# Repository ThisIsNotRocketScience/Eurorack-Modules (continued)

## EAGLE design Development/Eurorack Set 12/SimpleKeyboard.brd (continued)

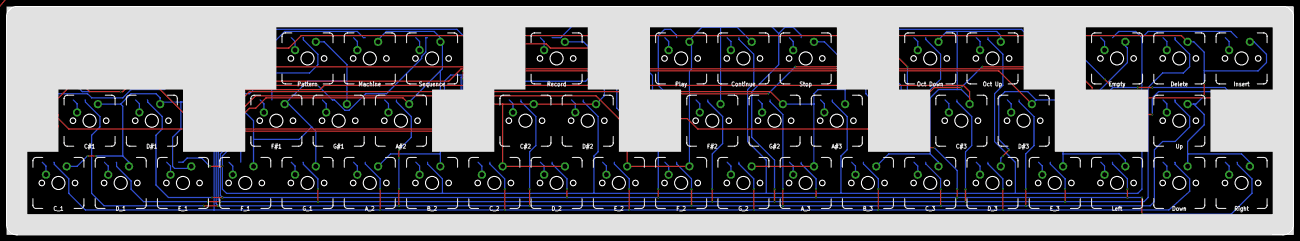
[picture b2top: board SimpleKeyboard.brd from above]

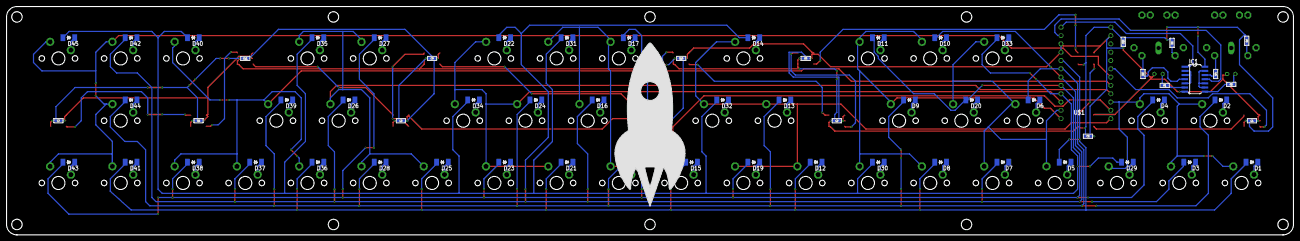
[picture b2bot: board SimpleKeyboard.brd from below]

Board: 2 copper layers, 393.7 x 69.8 mm, 152 parts (66 on the bottom side), 87 nets.

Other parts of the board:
U$45: ROCKET-5CM

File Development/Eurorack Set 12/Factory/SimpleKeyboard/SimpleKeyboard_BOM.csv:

Comment,Designator,Footprint,LCSC Part #
CGRM4001-G,"D1, D10, D11, D12, D13, D14, D15, D16, D17, D18, D19, D2, D20, D21, D22, D23, D24, D25, D26, D27, D28, D3, D4, D5, D6, D7, D8, D9, D29, D30, D31, D32, D33, D34, D35, D36, D37, D38, D39, D40, D41, D42, D43, D44, D45",SOD-123_MINI-SMA,
ARDUINO_PRO_MICRO,"U$1",ARDUINO_PRO_MICRO,
WS2812B,"LED1, LED2, LED3, LED4, LED5, LED6, LED7, LED8, LED9, LED10, LED11, LED12",WS2812B,
100n,"C1, C2, C3, C4, C5, C6, C7, C8, C9, C10, C11, C12",C0603,
MIDIJACK,"U$4, U$11",CP-2350,
74AC04D,"IC1",SO14,
330,"R1, R2",R0603,
220,"R3, R4, R5, R6",R0603,
,"D46, D47",3MMLED,
BUBBLESDSA_1U,"U$15, U$16, U$17, U$18, U$19, U$20",BUBBLES,
BUBBLESDSA_1U_HALF,"U$21, U$22, U$33",BUBBLES_HALF,
BUBBLESINV,"U$28, U$29, U$30, U$31, U$32",BUBBLES_INV,
BUBBLESONE,"U$34, U$35, U$36, U$37, U$38, U$39, U$40, U$41, U$42, U$43, U$44",BUBBLES_ONE,
C_1,"SW46",MX1A-XXNW,
C#1,"SW47",MX1A-XXNW,
D_1,"SW48",MX1A-XXNW,
D#1,"SW49",MX1A-XXNW,
E_1,"SW50",MX1A-XXNW,
F_1,"SW51",MX1A-XXNW,
F#1,"SW52",MX1A-XXNW,
G_1,"SW53",MX1A-XXNW,
G#1,"SW54",MX1A-XXNW,
A_2,"SW55",MX1A-XXNW,
A#2,"SW56",MX1A-XXNW,
B_2,"SW57",MX1A-XXNW,
C_2,"SW58",MX1A-XXNW,
C#2,"SW59",MX1A-XXNW,
D_2,"SW60",MX1A-XXNW,
D#2,"SW61",MX1A-XXNW,
E_2,"SW62",MX1A-XXNW,
F_2,"SW63",MX1A-XXNW,
F#2,"SW64",MX1A-XXNW,
G_2,"SW65",MX1A-XXNW,
G#2,"SW66",MX1A-XXNW,
A_3,"SW67",MX1A-XXNW,
A#3,"SW68",MX1A-XXNW,
B_3,"SW69",MX1A-XXNW,
C_3,"SW70",MX1A-XXNW,
C#3,"SW71",MX1A-XXNW,
D_3,"SW72",MX1A-XXNW,
D#3,"SW73",MX1A-XXNW,
E_3,"SW74",MX1A-XXNW,
Right,"SW75",MX1A-XXNW,
Up,"SW76",MX1A-XXNW,
Down,"SW77",MX1A-XXNW,
Stop,"SW78",MX1A-XXNW,
Oct Down,"SW79",MX1A-XXNW,
Left,"SW80",MX1A-XXNW,
Play,"SW81",MX1A-XXNW,
Continue,"SW82",MX1A-XXNW,
Record,"SW83",MX1A-XXNW,
Empty,"SW84",MX1A-XXNW,
Oct Up,"SW85",MX1A-XXNW,
Delete,"SW86",MX1A-XXNW,
Insert,"SW87",MX1A-XXNW,
Sequence,"SW88",MX1A-XXNW,
Pattern,"SW89",MX1A-XXNW,
Machine,"SW90",MX1A-XXNW,

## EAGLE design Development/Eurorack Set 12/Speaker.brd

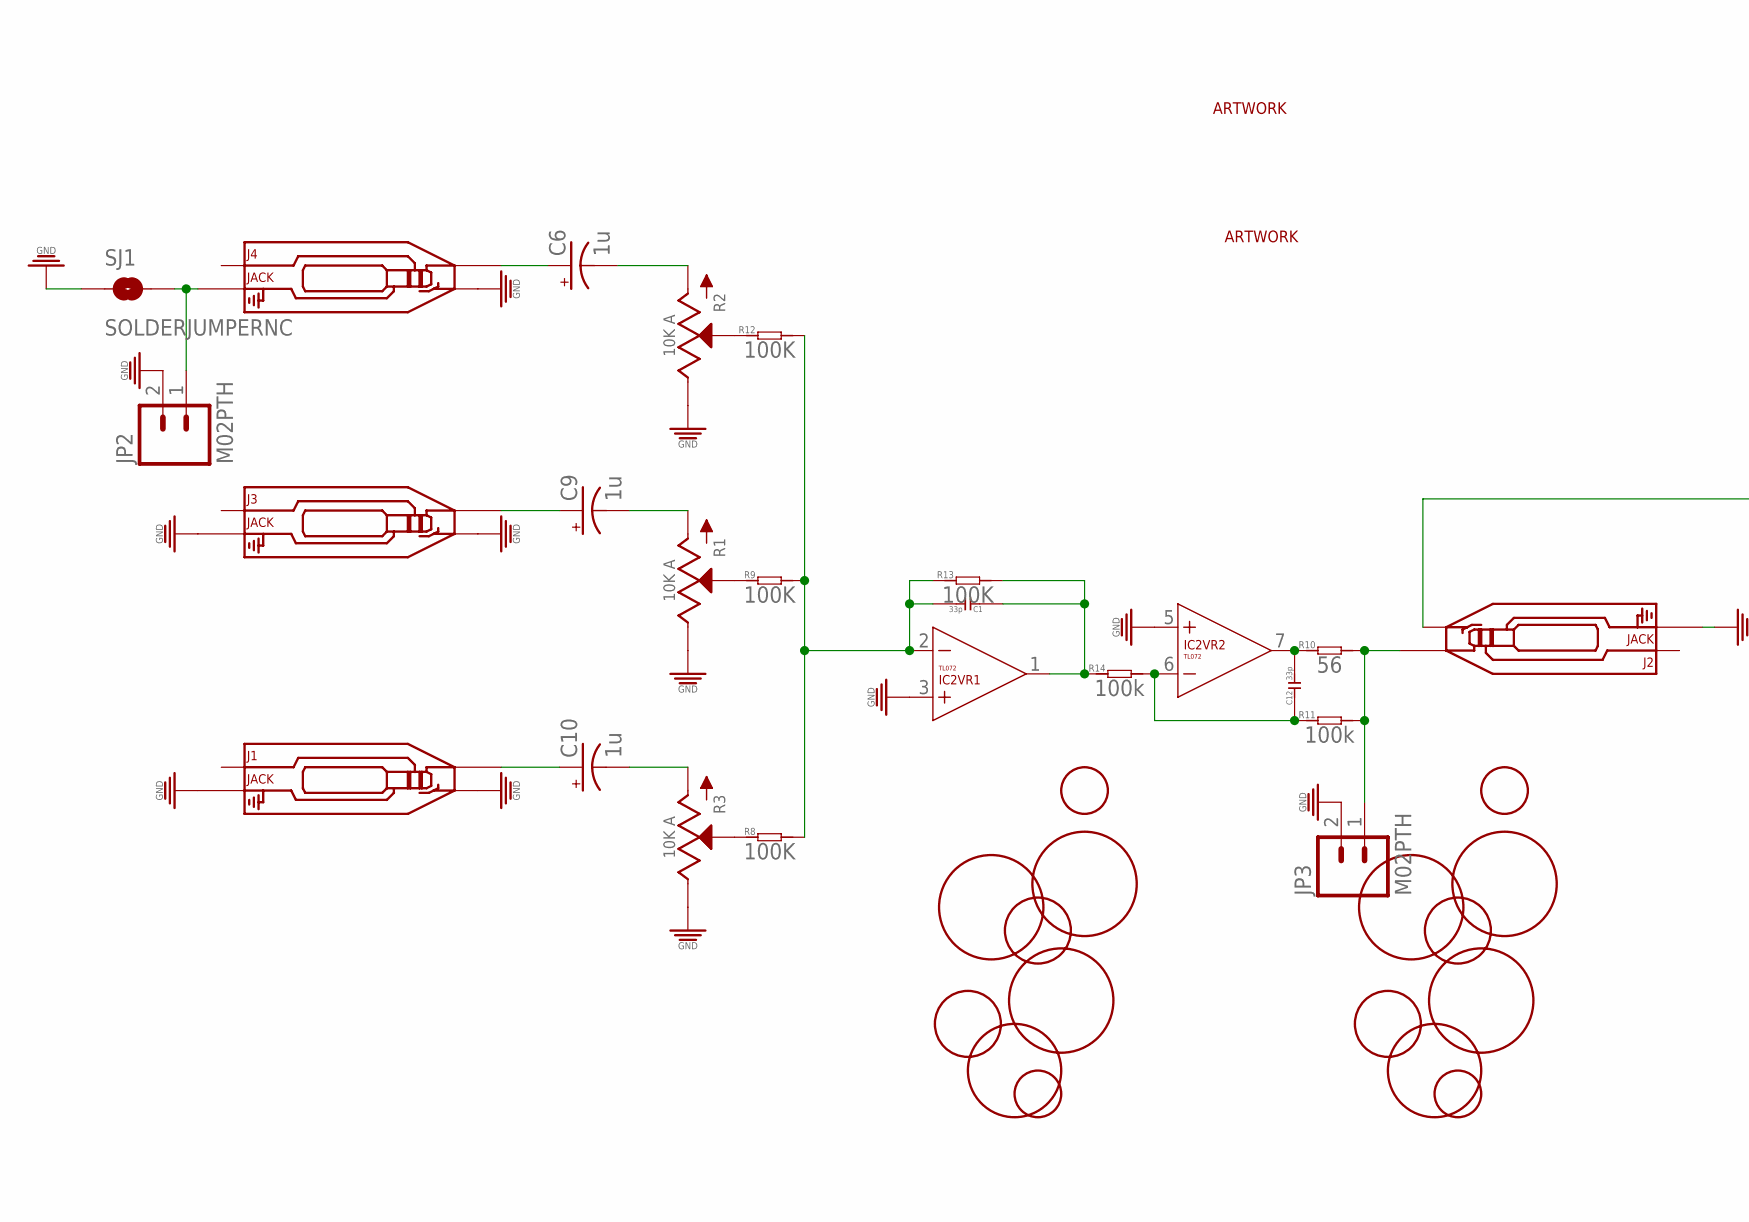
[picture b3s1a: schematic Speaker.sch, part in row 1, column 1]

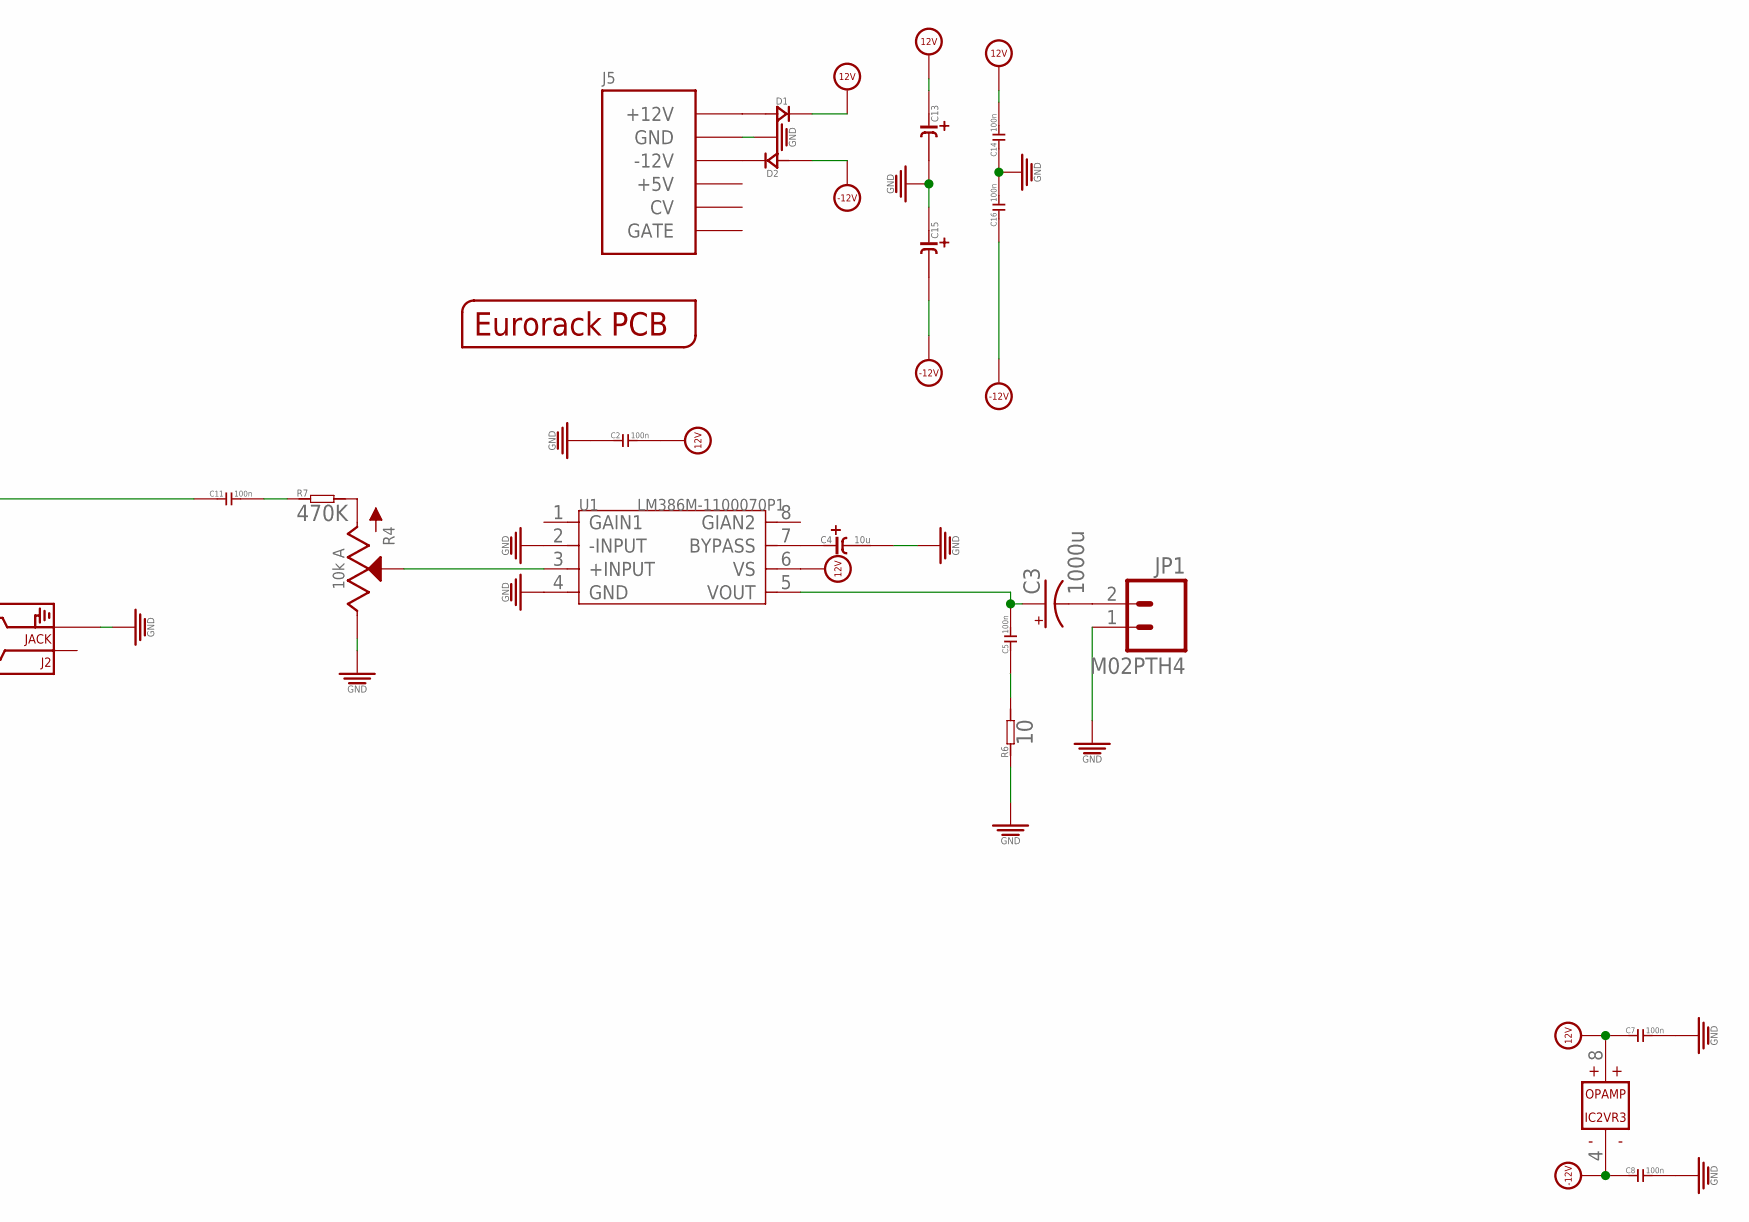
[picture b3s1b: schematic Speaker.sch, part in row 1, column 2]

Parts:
C1, C12: 33p; C0603
C2, C5, C7, C8, C11, C14, C16: 100n; C0603
C3: 1000u; 153CLV-1010
C4: 10u; CASE-A_3216
C6, C9, C10: 1u; PANASONIC_D
C13, C15: C-POLAR-A; CASE-A_3216
D1, D2: D-SOD-123; SOD123
IC2: TL072; SO08
J1, J2, J3, J4: JACK; 3.5MM-JACK-SWITCH-13MM-NOHOLES
J5: POWERSHROUDED; POWER_16_SHROUDED
JP1: M02PTH4; 1X02_XTRA_BIG
JP2, JP3: M02PTH; 1X02
PCB1: EURORACK_PCB6HP; EURORACK6HPPCB
R1, R2, R3: 10K A; ALPS_POT_SQUAREHOLES
R4: 10k A; ALPS_POT_SQUAREHOLES
R6: 10; R0603
R7: 470K; R0603
R8, R9, R12, R13: 100K; R0603
R10: 56; R0603
R11, R14: 100k; R0603
SJ1: SOLDERJUMPERNC; SJ_2S
U1: LM386M-1100070P1; SOIC8
U$1: BUBBLESDSA_1U; BUBBLES
U$8: BUBBLESINV; BUBBLES_INV
U$13: TINRS_ARTWORKTINYDATE; JUSTATINYROCKET_DATECODE
U$14: TINRS_ARTWORKLOGO; TINRSLOGO

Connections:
12V: C2.2, C7.1, C13.+ (1), C14.2, D1.-, IC2.8 (V+), U1.6 (VS)
-12V: C8.1, C15.- (2), C16.1, D2.+, IC2.4 (V-)
GND: C2.1, C4.- (2), C7.2, C8.2, C13.- (2), C14.1, C15.+ (1), C16.2, IC2.3 (+IN), IC2.5 (+IN), J1.RING_B@1 (RING), J1.RING_T@3 (RING), J1.SWITCH_B@1 (SWITCH), J1.SWITCH_T@3 (SWITCH), J2.RING_B@1 (RING), J2.RING_T@3 (RING), J3.RING_B@1 (RING), J3.RING_T@3 (RING), J3.SWITCH_B@1 (SWITCH), J3.SWITCH_T@3 (SWITCH), J4.SWITCH_B@1 (SWITCH), J4.SWITCH_T@3 (SWITCH), J5.3 (GND), J5.4 (GND), J5.5 (GND), J5.6 (GND), J5.7 (GND), J5.8 (GND), JP1.1, JP2.2, JP3.2, R1.P$1 (E), R2.P$1 (E), R3.P$1 (E), R4.P$1 (E), R6.1, SJ1.1, U1.2 (-INPUT), U1.4 (GND)
unnamed: C3.-, JP1.2
unnamed: C3.+, C5.2, U1.5 (VOUT)
unnamed: C5.1, R6.2
unnamed: C4.+ (1), U1.7 (BYPASS)
unnamed: R4.P$2 (S), U1.3 (+INPUT)
unnamed: C1.2, IC2.2 (-IN), R8.2, R9.2, R12.2, R13.1
unnamed: C12.1, IC2.6 (-IN), R11.1, R14.2
unnamed: C6.+, J4.TIP_B@1 (TIP), J4.TIP_T@3 (TIP)
unnamed: C11.2, R7.1
unnamed: C9.+, J3.TIP_B@1 (TIP), J3.TIP_T@3 (TIP)
unnamed: C10.+, J1.TIP_B@1 (TIP), J1.TIP_T@3 (TIP)
unnamed: C11.1, J2.SWITCH_B@1 (SWITCH), J2.SWITCH_T@3 (SWITCH)
unnamed: C12.2, IC2.7 (OUT), R10.1
unnamed: J2.TIP_B@1 (TIP), J2.TIP_T@3 (TIP), JP3.1, R10.2, R11.2
unnamed: R4.P$3 (A), R7.2
unnamed: R1.P$2 (S), R9.1
unnamed: R2.P$2 (S), R12.1
unnamed: R3.P$2 (S), R8.1
unnamed: C1.1, IC2.1 (OUT), R13.2, R14.1
unnamed: C10.-, R3.P$3 (A)
unnamed: C9.-, R1.P$3 (A)
unnamed: C6.-, R2.P$3 (A)
unnamed: D1.+, J5.9 (+12V), J5.10 (+12V)
unnamed: D2.-, J5.1 (-12V), J5.2 (-12V)
unnamed: J4.RING_B@1 (RING), J4.RING_T@3 (RING), JP2.1, SJ1.2

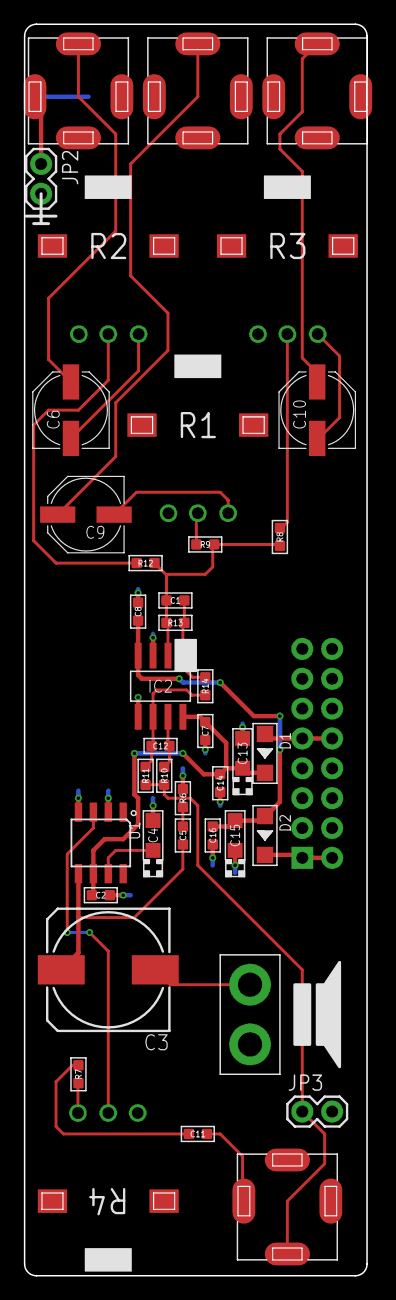
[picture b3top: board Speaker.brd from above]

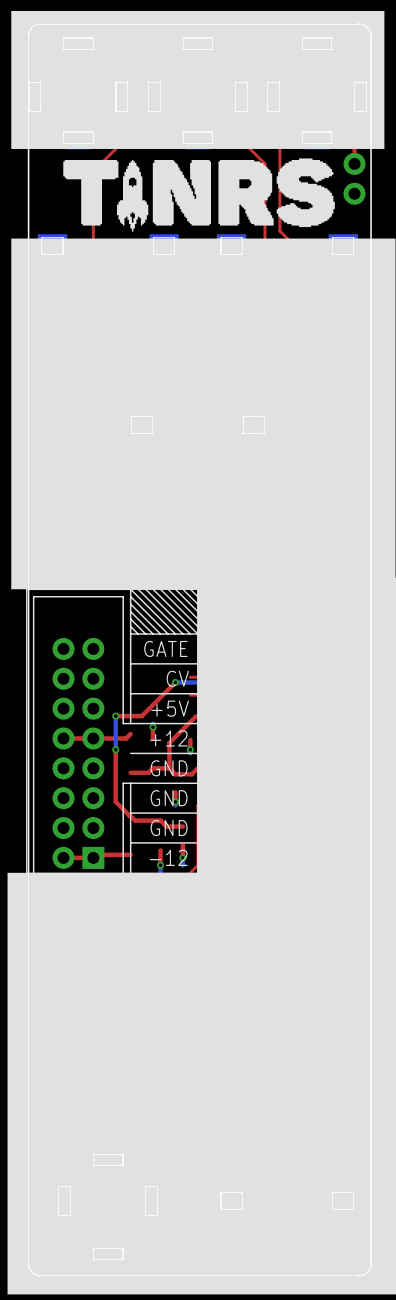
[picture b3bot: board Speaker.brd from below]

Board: 2 copper layers, 29.1 x 106.5 mm, 47 parts (4 on the bottom side), 28 nets.

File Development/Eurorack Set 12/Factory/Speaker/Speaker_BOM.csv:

Comment,Designator,Footprint,LCSC Part #
100n,"C2, C5, C7, C8, C11, C14, C16",C0603,
33p,"C12, C1",C0603,
1000u,"C3",153CLV-1010,
10u,"C4",CASE-A_3216,
,"C13, C15",CASE-A_3216,
JACK,"J1, J2, J3, J4",3.5MM-JACK-SWITCH-13MM-NOHOLES,
POWERSHROUDED,"J5",POWER_16_SHROUDED,
M02PTH4,"JP1",1X02_XTRA_BIG,
EURORACK_PCB6HP,"PCB1",EURORACK6HPPCB,
10K A,"R1, R2, R3",ALPS_POT_SQUAREHOLES,
10k A,"R4",ALPS_POT_SQUAREHOLES,
10,"R6",R0603,
470K,"R7",R0603,
56,"R10",R0603,
100k,"R11, R14",R0603,
100K,"R8, R9, R12, R13",R0603,
LM386M-1100070P1,"U1",SOIC8,
BUBBLESDSA_1U,"U$1",BUBBLES,
BUBBLESINV,"U$8",BUBBLES_INV,
1u,"C6, C9, C10",PANASONIC_D,
,"D1, D2",SOD123,
SOLDERJUMPERNC,"SJ1",SJ_2S,
M02PTH,"JP2, JP3",1X02,
TL072,"IC2",SO08,
TINRS_ARTWORKTINYDATE,"U$13",JUSTATINYROCKET_DATECODE,
TINRS_ARTWORKLOGO,"U$14",TINRSLOGO,

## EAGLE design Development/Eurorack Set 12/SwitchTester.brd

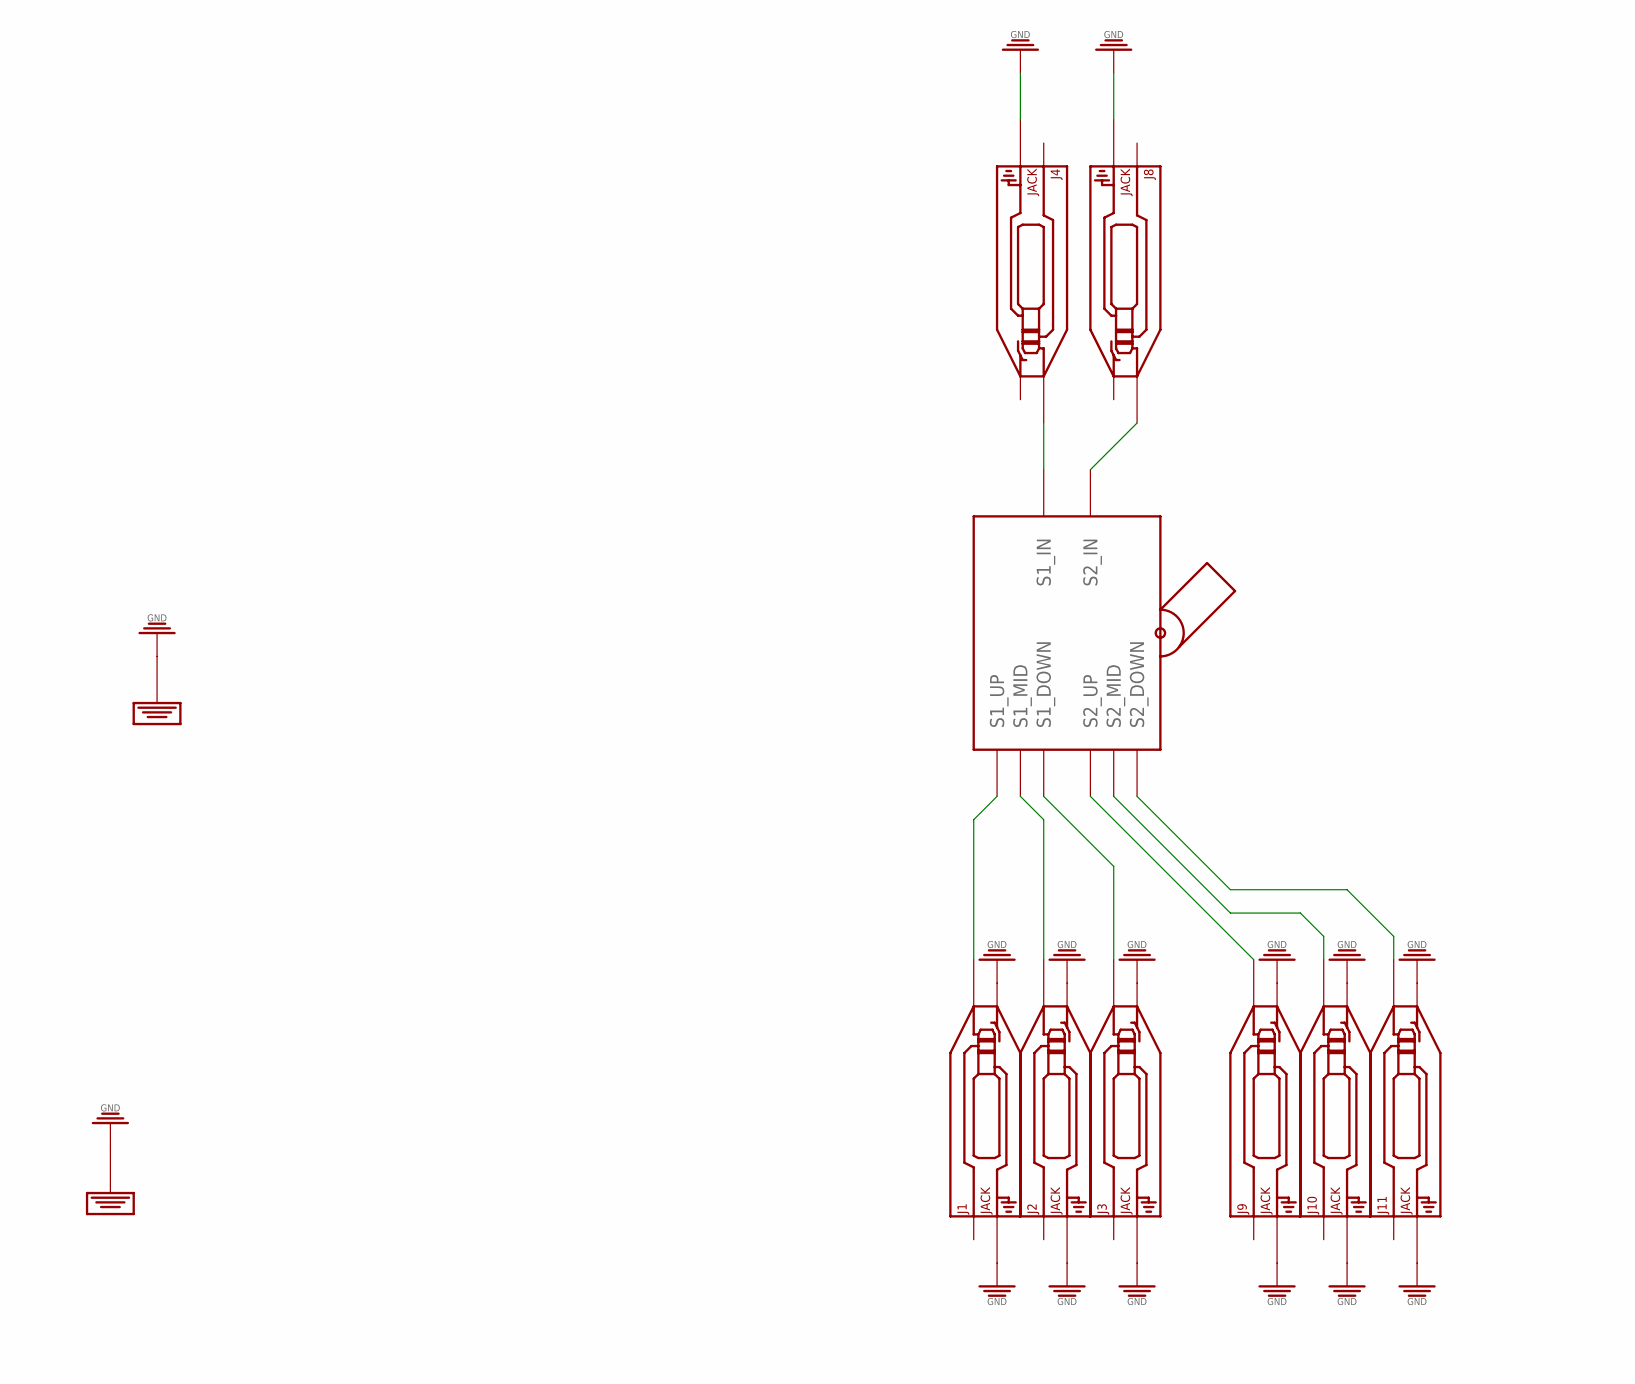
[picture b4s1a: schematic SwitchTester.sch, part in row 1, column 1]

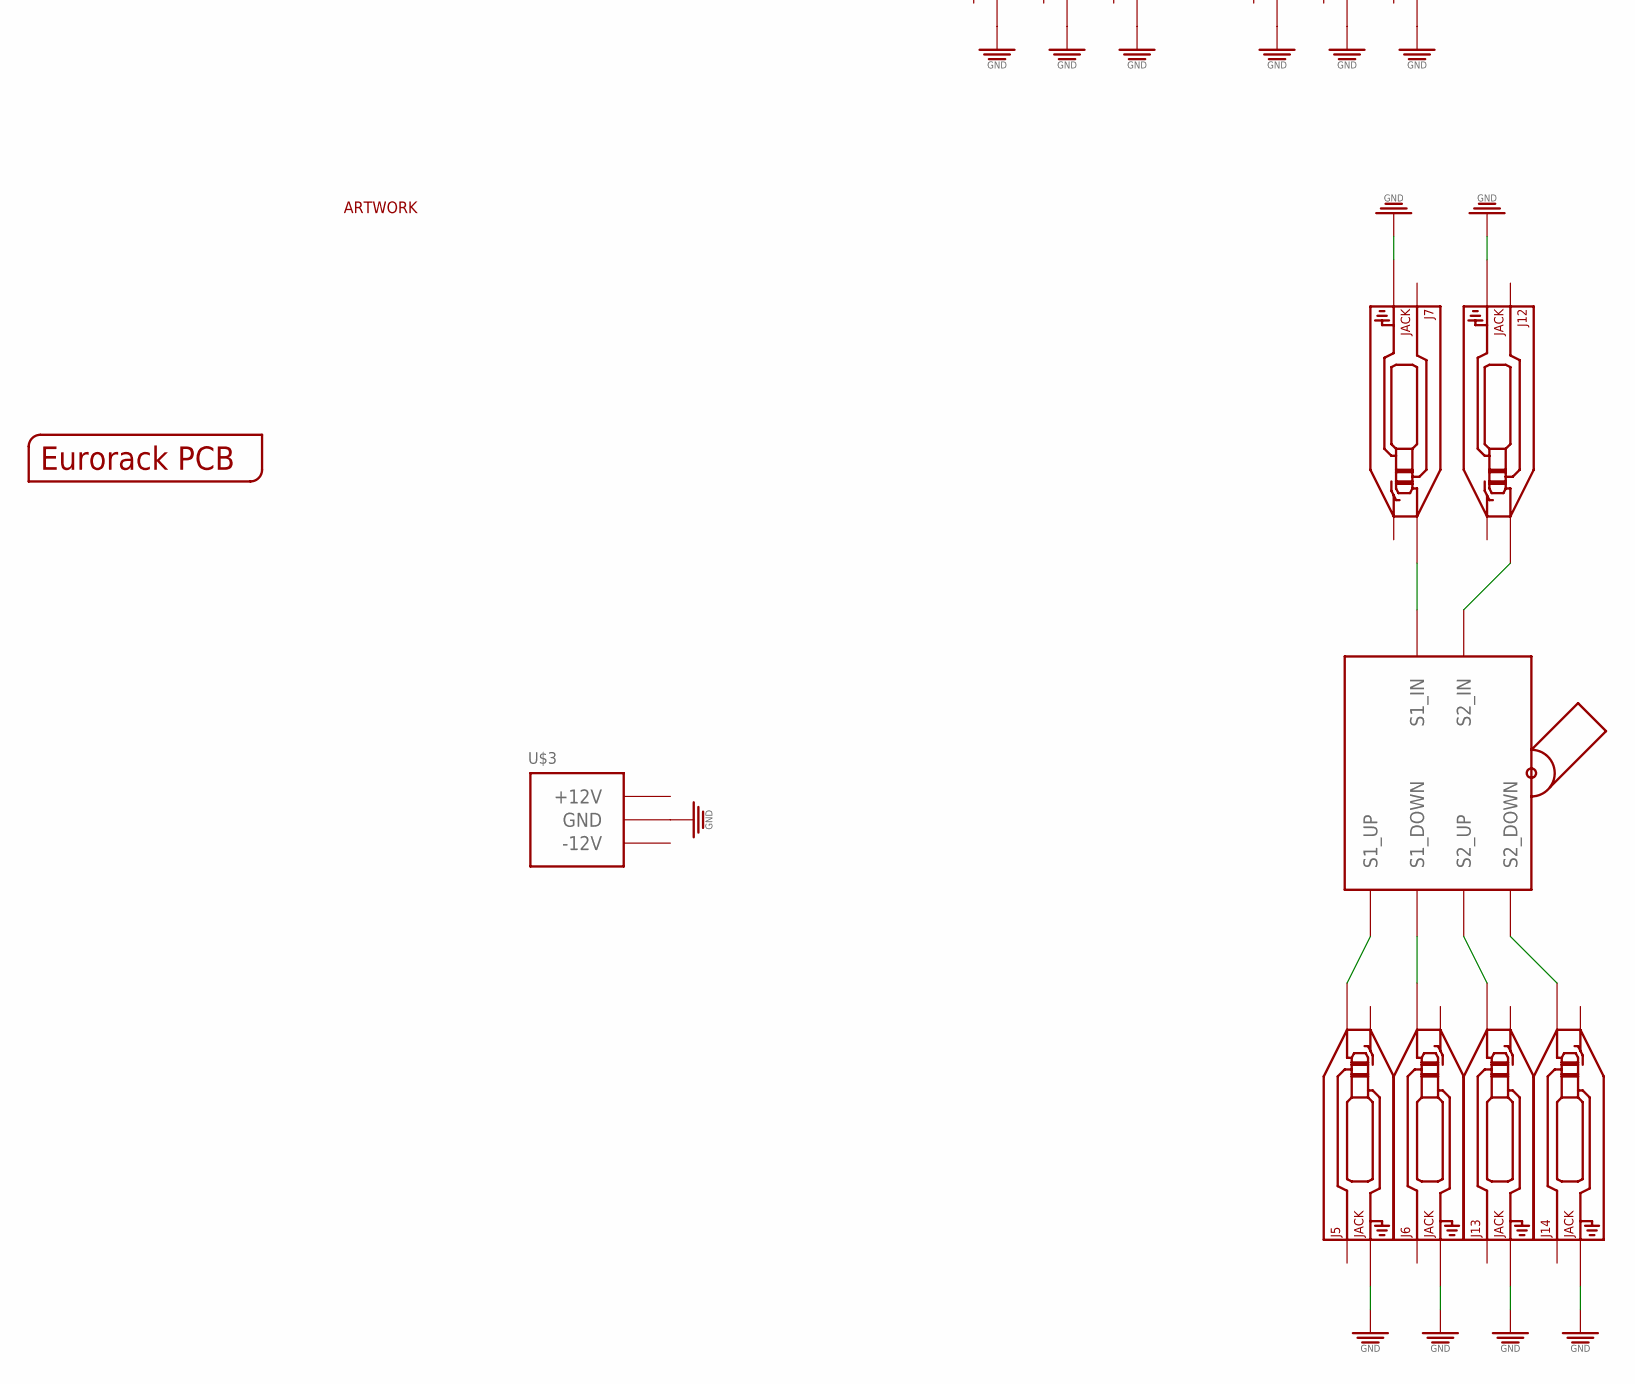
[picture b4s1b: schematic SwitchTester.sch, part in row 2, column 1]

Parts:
J1, J2, J3, J4, J5, J6, J7, J8, J9, J10, J11, J12, J13, J14: JACK; 3.5MM-JACK-SWITCH-13MM-NOHOLES
PCB1: EURORACK_PCB6HP; EURORACK6HPPCB
U$1: TS-22E01
U$2: TS-23E01
U$3: POWER_SIMPLE10; POWER_10
U$4: TINRS_ARTWORKTINYDATE; JUSTATINYROCKET_DATECODE

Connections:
GND: J1.RING_B@1 (RING), J1.RING_T@3 (RING), J1.SWITCH_B@1 (SWITCH), J1.SWITCH_T@3 (SWITCH), J2.RING_B@1 (RING), J2.RING_T@3 (RING), J2.SWITCH_B@1 (SWITCH), J2.SWITCH_T@3 (SWITCH), J3.RING_B@1 (RING), J3.RING_T@3 (RING), J3.SWITCH_B@1 (SWITCH), J3.SWITCH_T@3 (SWITCH), J4.RING_B@1 (RING), J4.RING_T@3 (RING), J5.RING_B@1 (RING), J5.RING_T@3 (RING), J6.RING_B@1 (RING), J6.RING_T@3 (RING), J7.RING_B@1 (RING), J7.RING_T@3 (RING), J8.RING_B@1 (RING), J8.RING_T@3 (RING), J9.RING_B@1 (RING), J9.RING_T@3 (RING), J9.SWITCH_B@1 (SWITCH), J9.SWITCH_T@3 (SWITCH), J10.RING_B@1 (RING), J10.RING_T@3 (RING), J10.SWITCH_B@1 (SWITCH), J10.SWITCH_T@3 (SWITCH), J11.RING_B@1 (RING), J11.RING_T@3 (RING), J11.SWITCH_B@1 (SWITCH), J11.SWITCH_T@3 (SWITCH), J12.RING_B@1 (RING), J12.RING_T@3 (RING), J13.RING_B@1 (RING), J13.RING_T@3 (RING), J14.RING_B@1 (RING), J14.RING_T@3 (RING), U$1.P$9 (GND), U$1.P$10 (GND), U$1.P$11 (GND), U$1.P$12 (GND), U$2.P$9 (GND), U$2.P$10 (GND), U$2.P$11 (GND), U$2.P$12 (GND), U$3.3 (GND), U$3.4 (GND), U$3.5 (GND), U$3.6 (GND), U$3.7 (GND), U$3.8 (GND)
unnamed: J4.TIP_B@1 (TIP), J4.TIP_T@3 (TIP), U$2.S1_SRC (S1_IN)
unnamed: J8.TIP_B@1 (TIP), J8.TIP_T@3 (TIP), U$2.S2_SRC (S2_IN)
unnamed: J1.TIP_B@1 (TIP), J1.TIP_T@3 (TIP), U$2.S1_UP
unnamed: J2.TIP_B@1 (TIP), J2.TIP_T@3 (TIP), U$2.S1_MID
unnamed: J3.TIP_B@1 (TIP), J3.TIP_T@3 (TIP), U$2.S1_DOWN
unnamed: J9.TIP_B@1 (TIP), J9.TIP_T@3 (TIP), U$2.S2_UP
unnamed: J10.TIP_B@1 (TIP), J10.TIP_T@3 (TIP), U$2.S2_MID
unnamed: J11.TIP_B@1 (TIP), J11.TIP_T@3 (TIP), U$2.S2_DOWN
unnamed: J6.TIP_B@1 (TIP), J6.TIP_T@3 (TIP), U$1.S1_DOWN, U$1.S1_DOWN1 (S1_DOWN)
unnamed: J5.TIP_B@1 (TIP), J5.TIP_T@3 (TIP), U$1.S1_UP, U$1.S1_UP1 (S1_UP)
unnamed: J7.TIP_B@1 (TIP), J7.TIP_T@3 (TIP), U$1.S1_SRC (S1_IN)
unnamed: J12.TIP_B@1 (TIP), J12.TIP_T@3 (TIP), U$1.S2_SRC (S2_IN)
unnamed: J13.TIP_B@1 (TIP), J13.TIP_T@3 (TIP), U$1.S2_UP, U$1.S2_UP1 (S2_UP)
unnamed: J14.TIP_B@1 (TIP), J14.TIP_T@3 (TIP), U$1.S2_DOWN, U$1.S2_DOWN1 (S2_DOWN)

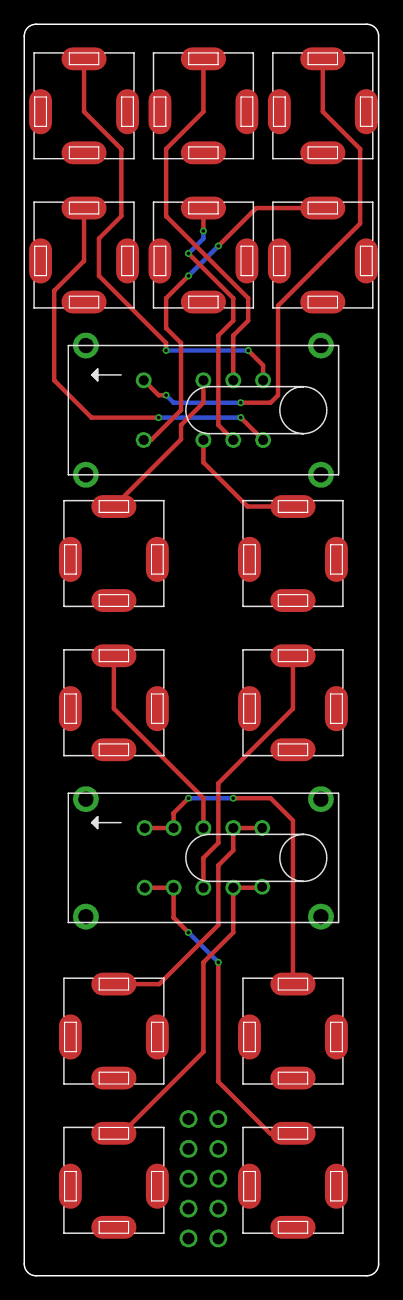
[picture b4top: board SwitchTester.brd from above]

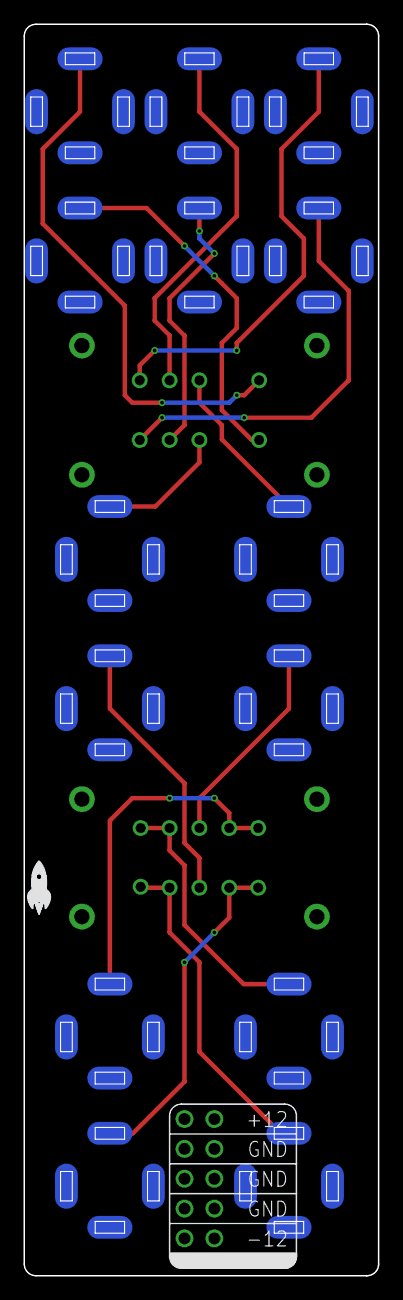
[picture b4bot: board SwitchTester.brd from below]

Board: 2 copper layers, 30.2 x 106.5 mm, 19 parts (2 on the bottom side), 15 nets.
